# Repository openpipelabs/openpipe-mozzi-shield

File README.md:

OpenPipe Mozzi Shield
========================

This is the PCB for the OpenPipe Mozzi Shield  
Format is EagleCAD schematic and board layout  

For more details, check out the product page at  
http://openpipe.cc/products/mozzi-shield/

OpenPipe invests time and resources providing this open source design, 
please support OpenPipe and open-source hardware by purchasing 
products from OpenPipe!

License & Attribution
---------------------
Designed by OpenPipe (www.openpipe.cc).

Creative Commons Attribution-NonCommercial-ShareAlike license (CC BY-NC-SA)

http://creativecommons.org/licenses/by-nc-sa/3.0/  
http://creativecommons.org/licenses/by-nc-sa/3.0/legalcode

All text above must be included in any redistribution

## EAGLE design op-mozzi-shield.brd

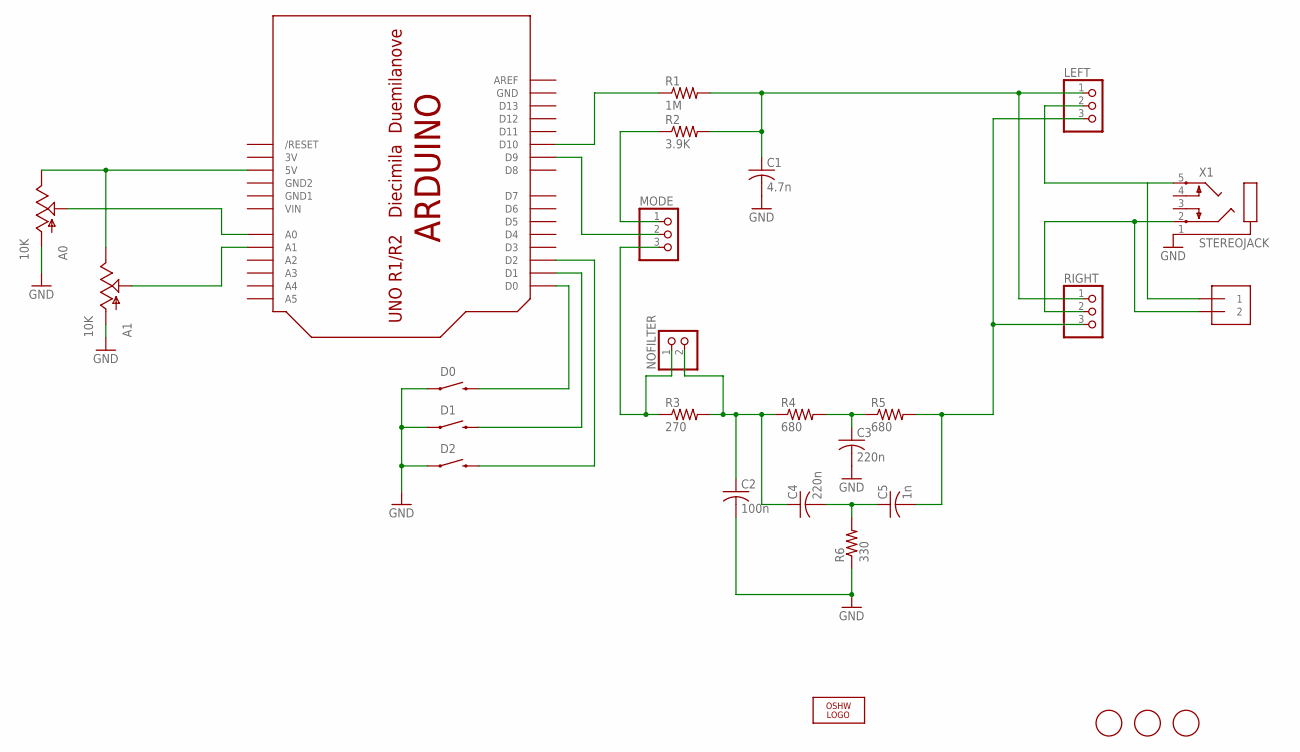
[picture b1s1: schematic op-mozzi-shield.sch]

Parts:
A0, A1: 10K; ALPS_POT
AUDIO: 1X2-3.5MM
C1: 4.7n; C0805
C2: 100n; C0805
C3, C4: 220n; C0805
C5: 1n; C0805
D0, D1, D2: SWITCH-MOMENTARY-212MM; TACTILE-PTH-12MM
LEFT: PINHD-1X3; 1X03
LOGO1: OSHW_LOGO_FILLX0200-NT; OSHW_FILLX200_NOTEXT
MODE: PINHD-1X3; 1X03
NOFILTER: PINHD-1X2; 1X02
R1: 1M; R0805
R2: 3.9K; R0805
R3: 270; R0805
R4, R5: 680; R0805
R6: 330; R0805
RIGHT: PINHD-1X3; 1X03
U$1: ARDUINO-NODIM
U$4, U$5, U$6: FIDUCIAL; FIDUCIAL_1MM
X1: STEREOJACK; STX3100

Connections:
3V: U$1.3V
GND: A0.P$3 (A), A1.P$3 (A), C1.2, C2.2, C3.2, D0.1, D1.1, D2.1, R6.1, U$1.GND, X1.1
GND1: U$1.GND1
GND2: U$1.GND2
unnamed: AUDIO.1, LEFT.2, X1.5
unnamed: AUDIO.2, RIGHT.2, X1.2
unnamed: C1.1, LEFT.1, R1.2, R2.2, RIGHT.1
unnamed: C2.1, C4.1, NOFILTER.2, R3.2, R4.1
unnamed: C4.2, C5.1, R6.2
unnamed: C3.1, R4.2, R5.1
unnamed: C5.2, LEFT.3, R5.2, RIGHT.3
unnamed: R1.1, U$1.D10
unnamed: MODE.2, U$1.D9
unnamed: MODE.1, R2.1
unnamed: MODE.3, NOFILTER.1, R3.1
unnamed: A0.P$2 (S), U$1.A0
unnamed: A1.P$2 (S), U$1.A1
unnamed: A0.P$1 (E), A1.P$1 (E), U$1.5V
unnamed: D0.3 (2), U$1.D0
unnamed: D1.3 (2), U$1.D1
unnamed: D2.3 (2), U$1.D2
VIN: U$1.VIN

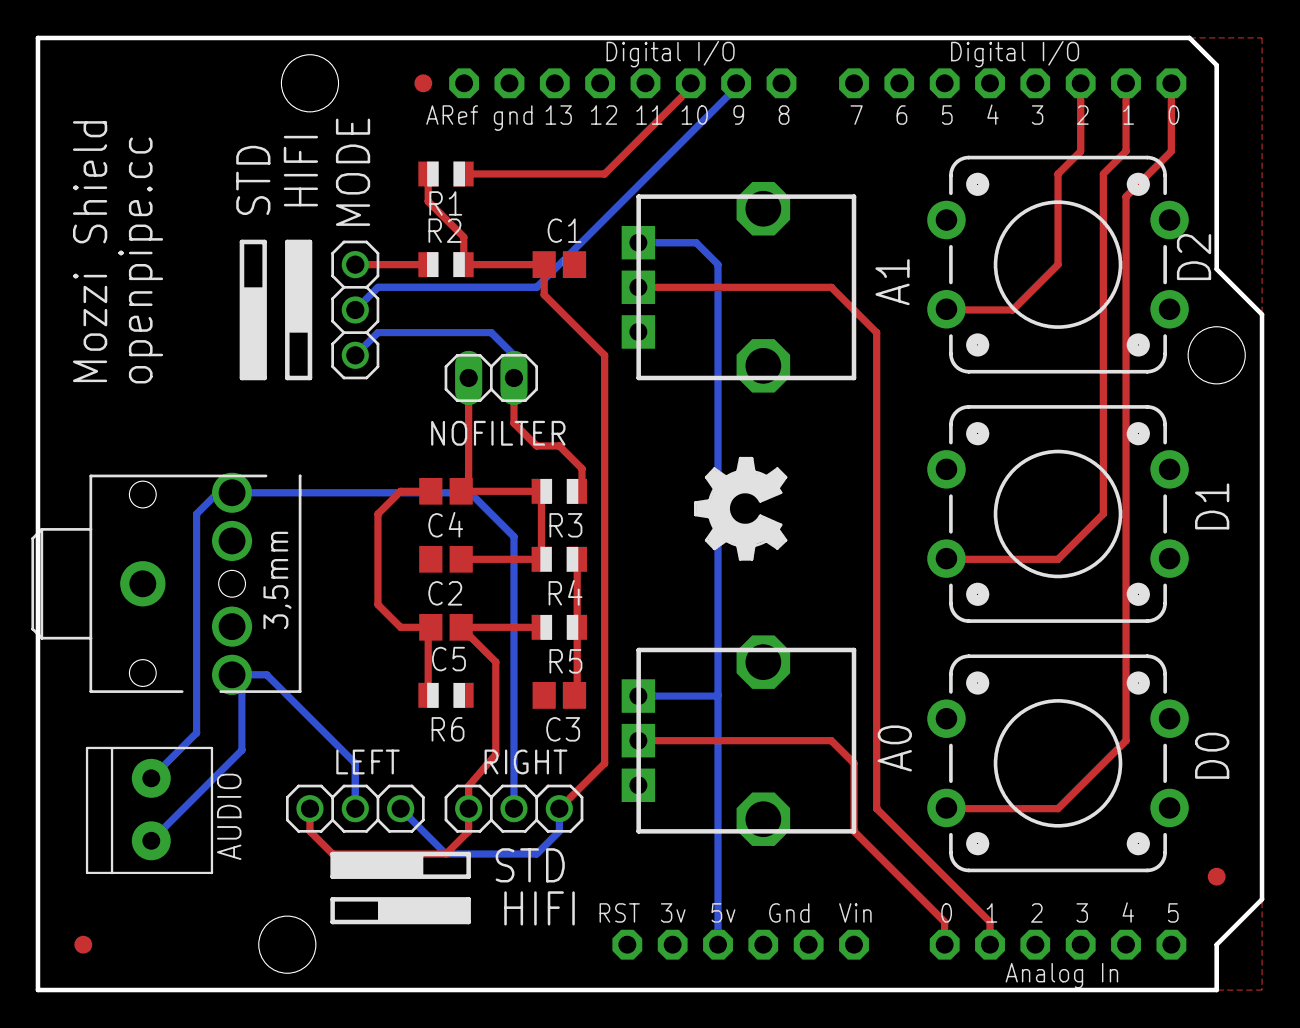
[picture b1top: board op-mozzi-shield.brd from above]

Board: 2 copper layers, 68.6 x 53.3 mm, 27 parts (0 on the bottom side), 18 nets.

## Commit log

2013-12-08 pdf caption removed
2013-12-08 README added

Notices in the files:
parts and their libraries:
SparkFun-Electromechanical: Licensing: CC v3.0 Share-Alike You are welcome to use this library for commercial purposes.
